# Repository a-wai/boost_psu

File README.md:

# Boost PSU for tube preamplifiers

This power supply is based on a MC34063A DC/DC converter. It can output up to 300V from a 12V DC input.

### Copyright

Copyright 2019, LEMON Amps.
Copyright 2019, Arnaud Ferraris.

This documentation describes Open Hardware and is licensed under the
CERN OHL v.1.2.

You may redistribute and modify this documentation under the terms of the
[CERN OHL v.1.2](http://ohwr.org/cernohl). This documentation is distributed
WITHOUT ANY EXPRESS OR IMPLIED WARRANTY, INCLUDING OF MERCHANTABILITY,
SATISFACTORY QUALITY AND FITNESS FOR A PARTICULAR PURPOSE.

Please see the CERN OHL v.1.2 for applicable conditions.

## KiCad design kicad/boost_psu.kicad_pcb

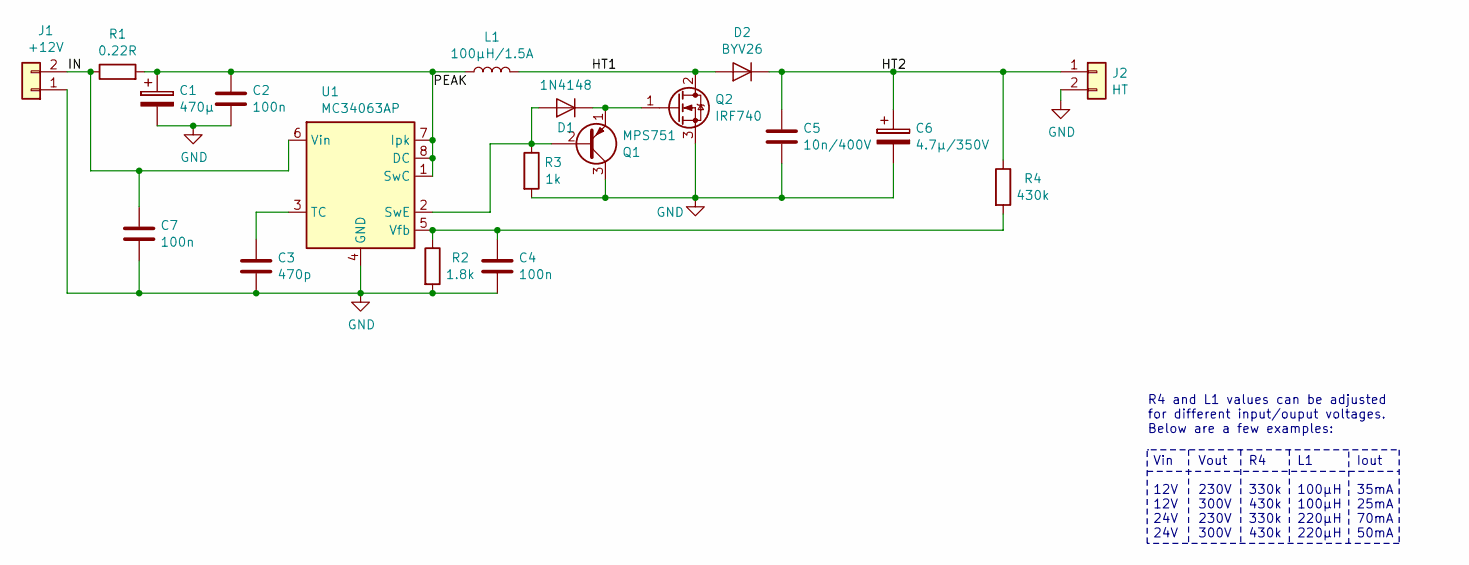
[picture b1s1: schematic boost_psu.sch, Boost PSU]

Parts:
C1: 470µ; CP_Radial_D10.0mm_P5.00mm; MPN UVR1V471MPD
C2, C4, C7: 100n; C_Rect_L7.2mm_W3.0mm_P5.00mm_FKS2_FKP2_MKS2_MKP2; MPN MKS2D031001A00KI00
C3: 470p; C_Disc_D6.0mm_W4.4mm_P5.00mm; MPN C322C471J2G5TA
C5: 10n/400V; C_Disc_D6.0mm_W4.4mm_P5.00mm; MPN C322C103KBR5TA
C6: 4.7µ/350V; CP_Radial_D10.0mm_P5.00mm; MPN UBT2V4R7MPD8
D1: 1N4148; D_DO-35_SOD27_P7.62mm_Horizontal; MPN 1N4148TR
D2: BYV26; D_DO-15_P10.16mm_Horizontal; MPN BYV26E-TAP
J1: +12V; TerminalBlock_bornier-2_P5.08mm; MPN 691102710002
J2: HT; TerminalBlock_bornier-2_P5.08mm; MPN 691102710002
L1: 100µH/1.5A; L_Radial_D10.5mm_P5.00mm_MuRATA_1200RS; MPN 12RS104C
Q1: MPS751; TO-92_Inline_Wide; MPN MPS751G
Q2: IRF740; TO-220-3_Vertical; MPN IRF740LCPBF
R1: 0.22R; R_Axial_DIN0207_L6.3mm_D2.5mm_P7.62mm_Horizontal; MPN LR1F220R
R2: 1.8k; R_Axial_DIN0207_L6.3mm_D2.5mm_P7.62mm_Horizontal; MPN LR1F1K8
R3: 1k; R_Axial_DIN0207_L6.3mm_D2.5mm_P7.62mm_Horizontal; MPN LR1F1K0
R4: 430k; R_Axial_DIN0207_L6.3mm_D2.5mm_P7.62mm_Horizontal; MPN YR1B432KCC
U1: MC34063AP; DIP-8_W7.62mm_LongPads; MPN MC34063AP1G

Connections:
/HT1: D2.2 (A), L1.2, Q2.2 (D)
/HT2: C5.1, C6.1, D2.1 (K), J2.1, R4.1
/IN: C7.1, J1.2, R1.1, U1.6 (Vin)
/PEAK: C1.1, C2.1, L1.1, R1.2, U1.1 (SwC), U1.7 (Ipk), U1.8 (DC)
GND: C1.2, C2.2, C3.2, C4.2, C5.2, C6.2, C7.2, J1.1, J2.2, Q1.3 (C), Q2.3 (S), R2.2, R3.2, U1.4 (GND)
unnamed: C3.1, U1.3 (TC)
unnamed: C4.1, R2.1, R4.2, U1.5 (Vfb)
unnamed: D1.1 (K), Q1.1 (E), Q2.1 (G)
unnamed: D1.2 (A), Q1.2 (B), R3.1, U1.2 (SwE)

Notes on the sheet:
Vin 12V 12V 24V 24V
Vout 230V 300V 230V 300V
R4 330k 430k 330k 430k
L1 100µH 100µH 220µH 220µH
Iout 35mA 25mA 70mA 50mA
R4 and L1 values can be adjusted for different input/ouput voltages. Below are a few examples:

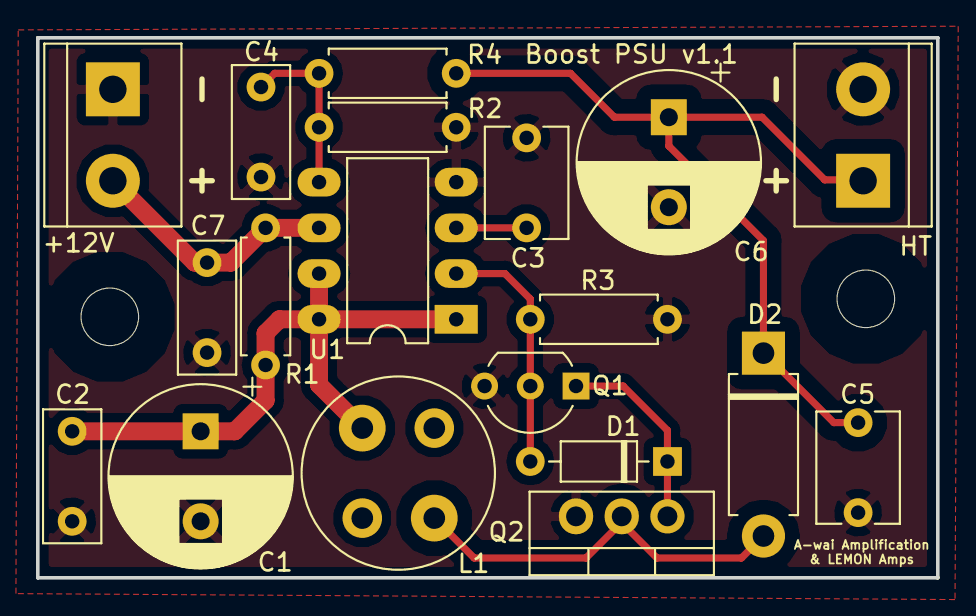
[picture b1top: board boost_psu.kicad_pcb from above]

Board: 2 copper layers, 50.0 x 30.0 mm, 19 parts (0 on the bottom side), 9 nets.

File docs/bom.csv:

Component,Description,References,Value,Quantity Per PCB,MFR,MPN,SPR,SPN
1,Unpolarized capacitor,C2 C4 C7,100n,3,WIMA,MKS2D031001A00KI00,RS,108-2700
2,Unpolarized capacitor,C5,10n/400V,1,KEMET,C322C103KBR5TA,RS,906-0654
3,Polarized capacitor,C6,4.7µ/350V,1,Nichicon,UBT2V4R7MPD8,RS,762-189
4,Unpolarized capacitor,C3,470p,1,KEMET,C322C471J2G5TA,RS,538-1534
5,Polarized capacitor,C1,470µ,1,Nichicon,UVR1V471MPD,RS,862-3370
6,Diode,D1,1N4148,1,ON Semiconductor,1N4148TR,RS,671-5477
7,Diode,D2,BYV26,1,Vishay,BYV26E-TAP,RS,708-7776
8,"Generic connector, single row, 01x02, script generated (kicad-library-utils/schlib/autogen/connector/)",J1,+12V,1,Wurth Elektronik,691102710002,RS,826-7226
9,"Generic connector, single row, 01x02, script generated (kicad-library-utils/schlib/autogen/connector/)",J2,HT,1,Wurth Elektronik,691102710002,RS,826-7226
10,Inductor,L1,100µH/1.5A,1,Murata Power Solutions,12RS104C,RS,715-7374
11,"10A Id, 400V Vds, N-Channel Power MOSFET, 500mOhm Rds, TO-220AB",Q2,IRF740,1,Vishay,IRF740LCPBF,RS,536-5992
12,"PNP transistor, emitter/base/collector",Q1,MPS751,1,ON Semiconductor,MPS751G,RS,774-3583
13,Resistor,R1,0.22R,1,TE Connectivity,LR1F220R,RS,148-348
14,Resistor,R2,1.8k,1,TE Connectivity,LR1F1K8,RS,148-562
15,Resistor,R3,1k,1,TE Connectivity,LR1F1K0,RS,125-1159
16,Resistor,R4,430k,1,TE Connectivity,YR1B432KCC,RS,754-5753
17,"1.5A, step-up/down/inverting switching regulator, 3-40V Vin, 100kHz, DIP-8",U1,MC34063AP,1,ON Semiconductor,MC34063AP1G,RS,516-5095

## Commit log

2019-03-07 Add license files
2019-03-07 Add project information
2019-03-07 Add calculation spreadsheet
2019-03-07 Improve calculation spreadsheet
2019-03-09 Improve schematic & PCB routing
    - put filtering capacitors on the switch collector rather than Vin
    - add a 100n filtering capacitor on Vin
    - switch to a 30x50mm board for a better layout
    - add LEMON Amps as co-author
2019-03-09 Add emphasis in spreadsheet when exceeding max current
2019-03-09 Change IRF740 orientation
    As the MPSA55 is pretty close, it is better for the IRF740 tab to face
    outwards, in order not to dissipate heat towards the transistor.
2019-03-10 Change a few footprints and rework schematics
2019-03-10 Rename PDF schematics file
2019-03-10 Update schematics PDF
2019-03-10 Fix transistor polarity
2019-03-11 Add BOM
2019-03-11 Move BOM files for serving through GH pages
2019-03-11 Add PCB rendering image
2019-03-11 Fix README
2019-03-15 Fix inductor footprint & improve layout
2019-03-15 Fix some markings orientations on silkscreen
2019-03-30 Fix supplier refs in BOM
2019-04-25 Update BOM logo
2019-04-26 Fix R1 Manufacturer & Supplier Part Nr.

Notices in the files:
kicad/boost_psu.sch:
Licensed under CERN OHL v.1.2
